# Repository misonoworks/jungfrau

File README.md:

# jungfrau
A 80-ish% Alps keyboard with an LED bar

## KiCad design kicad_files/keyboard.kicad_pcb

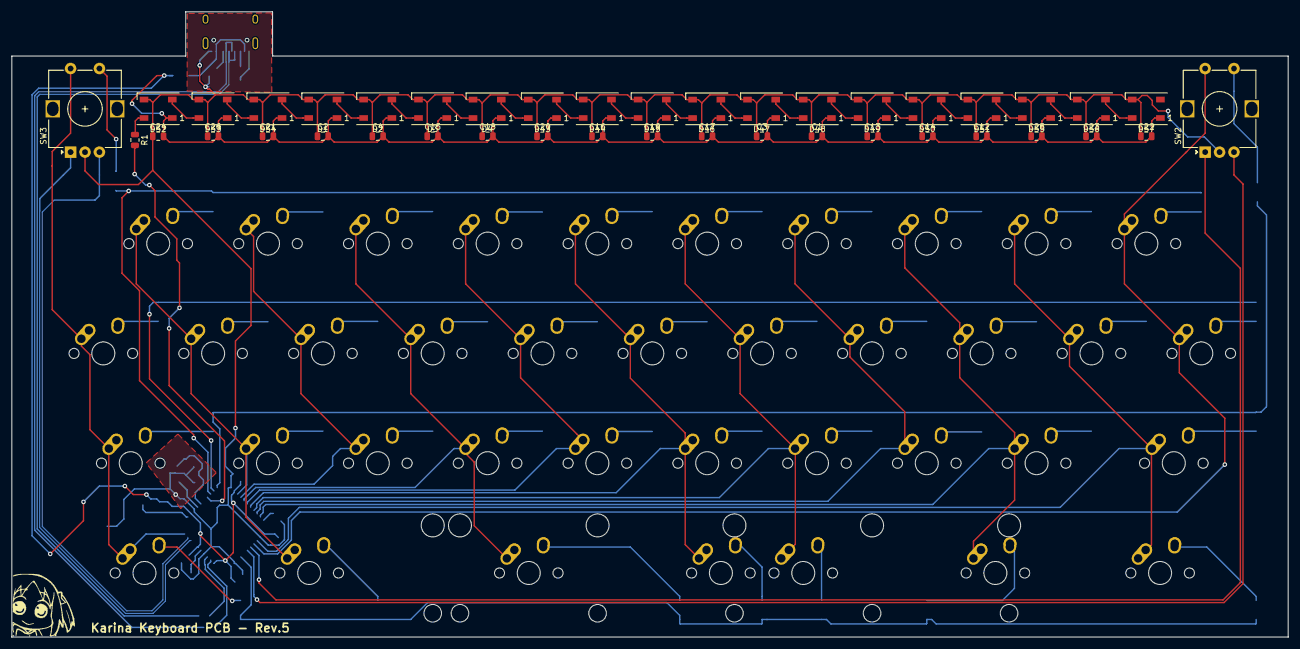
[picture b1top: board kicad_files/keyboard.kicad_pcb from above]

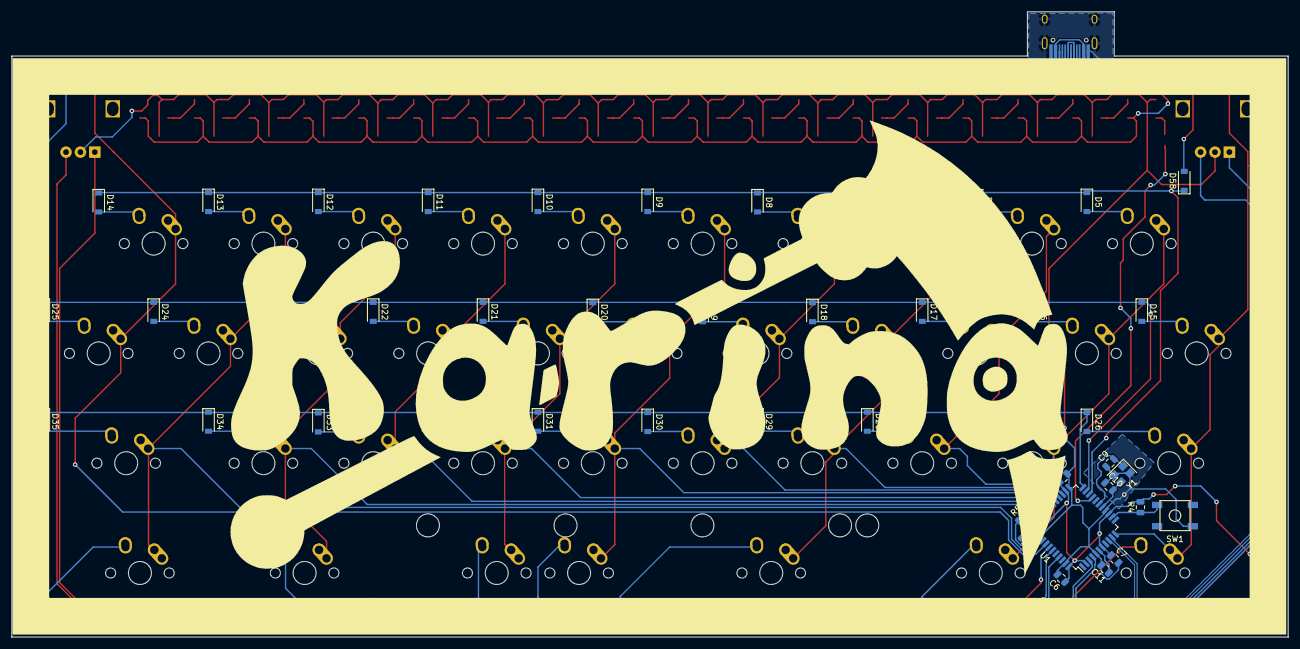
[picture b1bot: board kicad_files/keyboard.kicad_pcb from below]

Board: 2 copper layers, 221.5 x 108.5 mm, 137 parts (58 on the bottom side), 93 nets.

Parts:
C1, C2, C3, C4, C12, C13, C14, C15, C16, C17, C18, C19, C20, C21, C22, C23, C24, C25, C26: 104; C_0805_2012Metric
C5, C6, C7, C8, C11: 1uF; C_0805_2012Metric
C9, C10: 22pF; C_0805_2012Metric
D1, D2, D3, D4, D43, D44, D45, D46, D47, D48, D49, D50, D51, D52, D53, D54, D55, D56, D57: WS2812B; LED_WS2812B_PLCC4_5.0x5.0mm_P3.2mm
D5, D6, D7, D8, D9, D10, D11, D12, D13, D14, D15, D16, D17, D18, D19, D20, D21, D22, D23, D24, D25, D26, D27, D28, D29, D30, D31, D32, D33, D34, D35, D36, D37, D38, D39, D40, D41, D42, D58, D59: D_Small; D_SOD-123
F1: Polyfuse_Small; Fuse_1206_3216Metric
K_A1: MX-NoLED; MX-1U-NoLED
K_APO1: MX-NoLED; MX-1U-NoLED
K_B1: MX-NoLED; MX-1U-NoLED
K_C1: MX-NoLED; MX-1U-NoLED
K_D1: MX-NoLED; MX-1U-NoLED
K_E1: MX-NoLED; MX-1U-NoLED
K_F1: MX-NoLED; MX-1U-NoLED
K_G1: MX-NoLED; MX-1U-NoLED
K_H1: MX-NoLED; MX-1U-NoLED
K_I1: MX-NoLED; MX-1U-NoLED
K_J1: MX-NoLED; MX-1U-NoLED
K_K1: MX-NoLED; MX-1U-NoLED
K_L1: MX-NoLED; MX-1U-NoLED
K_LCTRL1: MX-NoLED; MX-1.75U-NoLED
K_M1: MX-NoLED; MX-1U-NoLED
K_META1: MX-NoLED; MX-1.75U-NoLED
K_N1: MX-NoLED; MX-1U-NoLED
K_O1: MX-NoLED; MX-1U-NoLED
K_P1: MX-NoLED; MX-1U-NoLED
K_PERIOD1: MX-NoLED; MX-1U-NoLED
K_Q1: MX-NoLED; MX-1U-NoLED
K_R1: MX-NoLED; MX-1U-NoLED
K_S1: MX-NoLED; MX-1U-NoLED
K_SHIFT1, K_SHIFT2: MX-NoLED; MX-1.5U-NoLED
K_SPACEBARSIX1: MX-NoLED; MX-6.25U-ReversedStabilizers-NoLED
K_SPBALT1: MX-NoLED; MX-1.25U-NoLED
K_SPBDEL1: MX-NoLED; MX-2.25U-ReversedStabilizers-NoLED
K_SPBSPACE1: MX-NoLED; MX-2.75U-ReversedStabilizers-NoLED
K_SUPER1: MX-NoLED; MX-1.25U-NoLED
K_T1: MX-NoLED; MX-1U-NoLED
K_TAB1: MX-NoLED; MX-1U-NoLED
K_U1: MX-NoLED; MX-1U-NoLED
K_V1: MX-NoLED; MX-1U-NoLED
K_W1: MX-NoLED; MX-1U-NoLED
K_X1: MX-NoLED; MX-1U-NoLED
K_Y1: MX-NoLED; MX-1U-NoLED
K_Z1: MX-NoLED; MX-1U-NoLED
R1: 500ohm; R_0805_2012Metric
R2, R3: 22; R_0805_2012Metric
R4, R5: 10K; R_0805_2012Metric
R6, R7: 5.1k; R_0805_2012Metric
SW1: SW_Push; SKQG-1155865
SW2, SW3: Rotary_Encoder_Switch; RotaryEncoder_Alps_EC12E-Switch_Vertical_H20mm
U1: ATmega32U4-AU; TQFP-44_10x10mm_P0.8mm
USB1: HRO-TYPE-C-31-M-12; HRO-TYPE-C-31-M-12-HandSoldering
Y1: Crystal_GND24_Small; Crystal_SMD_3225-4Pin_3.2x2.5mm

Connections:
2812b_data: R1.2, U1.19
+5V: C1.2, C2.2, C3.2, C4.2, C5.1, C6.1, C7.1, C8.1, C12.2, C13.2, C14.2, C15.2, C16.2, C17.2, C18.2, C19.2, C20.2, C21.2, C22.2, C23.2, C24.2, C25.2, C26.2, D1.1, D2.1, D3.1, D4.1, D43.1, D44.1, D45.1, D46.1, D47.1, D48.1, D49.1, D50.1, D51.1, D52.1, D53.1, D54.1, D55.1, D56.1, D57.1, F1.1, R4.2, U1.2, U1.7, U1.14, U1.24, U1.34, U1.44
D+: R3.2, USB1.6, USB1.8
D-: R2.2, USB1.5, USB1.7
Encoder1D+: SW3.A, U1.9
Encoder1D-: SW3.B, U1.10
Encoder2D+: SW2.A, U1.38
Encoder2D-: SW2.B, U1.39
GND: C1.1, C2.1, C3.1, C4.1, C5.2, C6.2, C7.2, C8.2, C9.1, C10.1, C11.2, C12.1, C13.1, C14.1, C15.1, C16.1, C17.1, C18.1, C19.1, C20.1, C21.1, C22.1, C23.1, C24.1, C25.1, C26.1, D1.3, D2.3, D3.3, D4.3, D43.3, D44.3, D45.3, D46.3, D47.3, D48.3, D49.3, D50.3, D51.3, D52.3, D53.3, D54.3, D55.3, D56.3, D57.3, R5.1, R6.1, R7.1, SW1.1, SW2.C, SW3.C, U1.5, U1.15, U1.23, U1.35, U1.43, USB1.1, USB1.12, USB1.13, Y1.2, Y1.4
unnamed: C9.2, U1.17, Y1.1
unnamed: C10.2, U1.16, Y1.3
unnamed: C11.1, U1.6
unnamed: D1.2, D2.4
unnamed: D1.4, D54.2
unnamed: D2.2, D3.4
unnamed: D3.2, D4.4
unnamed: D4.2, D43.4
unnamed: D5.2, K_Q1.2
unnamed: D6.2, K_W1.2
unnamed: D7.2, K_E1.2
unnamed: D8.2, K_R1.2
unnamed: D9.2, K_T1.2
unnamed: D10.2, K_Y1.2
unnamed: D11.2, K_U1.2
unnamed: D12.2, K_I1.2
unnamed: D13.2, K_O1.2
unnamed: D14.2, K_P1.2
unnamed: D15.2, K_TAB1.2
unnamed: D16.2, K_A1.2
unnamed: D17.2, K_S1.2
unnamed: D18.2, K_D1.2
unnamed: D19.2, K_F1.2
unnamed: D20.2, K_G1.2
unnamed: D21.2, K_H1.2
unnamed: D22.2, K_J1.2
unnamed: D23.2, K_K1.2
unnamed: D24.2, K_L1.2
unnamed: D25.2, K_APO1.2
unnamed: D26.2, K_SHIFT1.2
unnamed: D27.2, K_Z1.2
unnamed: D28.2, K_X1.2
unnamed: D29.2, K_C1.2
unnamed: D30.2, K_V1.2
unnamed: D31.2, K_B1.2
unnamed: D32.2, K_N1.2
unnamed: D33.2, K_M1.2
unnamed: D34.2, K_PERIOD1.2
unnamed: D35.2, K_SHIFT2.2
unnamed: D36.2, K_LCTRL1.2
unnamed: D37.2, K_SUPER1.2
unnamed: D38.2, K_SPBSPACE1.2
unnamed: D39.2, K_SPACEBARSIX1.2
unnamed: D40.2, K_SPBDEL1.2
unnamed: D41.2, K_SPBALT1.2
unnamed: D42.2, K_META1.2
unnamed: D43.2, D44.4
unnamed: D44.2, D45.4
unnamed: D45.2, D46.4
unnamed: D46.2, D47.4
unnamed: D47.2, D48.4
unnamed: D48.2, D49.4
unnamed: D49.2, D50.4
unnamed: D50.2, D51.4
unnamed: D51.2, D55.4
unnamed: D52.2, D53.4
unnamed: D52.4, R1.1
unnamed: D53.2, D54.4
unnamed: D55.2, D56.4
unnamed: D56.2, D57.4
unnamed: D58.2, SW3.S2
unnamed: D59.2, SW2.S2
unnamed: R2.1, U1.3
unnamed: R3.1, U1.4
unnamed: R4.1, SW1.2, U1.13
unnamed: R5.2, U1.33
unnamed: R6.2, USB1.4
unnamed: R7.2, USB1.10
VCC: F1.2, USB1.2, USB1.11
col0: K_LCTRL1.1, K_SHIFT1.1, K_TAB1.1, SW3.S1, U1.11
col1: K_A1.1, K_Q1.1, K_SUPER1.1, K_Z1.1, U1.25
col2: K_S1.1, K_W1.1, K_X1.1, U1.26
col3: K_C1.1, K_D1.1, K_E1.1, K_SPBSPACE1.1, U1.27
col4: K_F1.1, K_R1.1, K_V1.1, U1.28
col5: K_B1.1, K_G1.1, K_SPACEBARSIX1.1, K_T1.1, U1.29
col6: K_H1.1, K_N1.1, K_SPBDEL1.1, K_Y1.1, U1.30
col7: K_J1.1, K_M1.1, K_U1.1, U1.31
col8: K_I1.1, K_K1.1, K_PERIOD1.1, K_SPBALT1.1, U1.32
col9: K_L1.1, K_META1.1, K_O1.1, K_SHIFT2.1, U1.36
col10: K_APO1.1, K_P1.1, SW2.S1, U1.37
row0: D5.1, D6.1, D7.1, D8.1, D9.1, D10.1, D11.1, D12.1, D13.1, D14.1, D58.1, U1.20
row1: D15.1, D16.1, D17.1, D18.1, D19.1, D20.1, D21.1, D22.1, D23.1, D24.1, D25.1, U1.21
row2: D26.1, D27.1, D28.1, D29.1, D30.1, D31.1, D32.1, D33.1, D34.1, D35.1, D59.1, U1.22
row3: D36.1, D37.1, D38.1, D39.1, D40.1, D41.1, D42.1, U1.41

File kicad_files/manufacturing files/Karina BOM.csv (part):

Date:,09/23/20 0:31:32,,,,,,
Tool:,Eeschema (5.1.5)-3,,,,,,
Component Count:,137,,,,,,
Ref,Value,Footprint,Datasheet,Manufacturer,Vendor,LCSC Part No.,Manufacturer Part No.
C1,104,Capacitor_SMD:C_0805_2012Metric,~,YAGEO,LCSC,C49678,CC0805KRX7R9BB104
C2,104,Capacitor_SMD:C_0805_2012Metric,~,YAGEO,LCSC,C49678,CC0805KRX7R9BB104
C3,104,Capacitor_SMD:C_0805_2012Metric,~,YAGEO,LCSC,C49678,CC0805KRX7R9BB104
C4,104,Capacitor_SMD:C_0805_2012Metric,~,YAGEO,LCSC,C49678,CC0805KRX7R9BB104
C5,1uF,Capacitor_SMD:C_0805_2012Metric,~,Samsung Electro-Mechanics,LCSC,C28323,CL21B105KBFNNNE
C6,1uF,Capacitor_SMD:C_0805_2012Metric,~,Samsung Electro-Mechanics,LCSC,C28323,CL21B105KBFNNNE
C7,1uF,Capacitor_SMD:C_0805_2012Metric,~,Samsung Electro-Mechanics,LCSC,C28323,CL21B105KBFNNNE
C8,1uF,Capacitor_SMD:C_0805_2012Metric,~,Samsung Electro-Mechanics,LCSC,C28323,CL21B105KBFNNNE
C9,22pF,Capacitor_SMD:C_0805_2012Metric,~,Samsung Electro-Mechanics,LCSC,C1804,CL21C220JBANNNC
C10,22pF,Capacitor_SMD:C_0805_2012Metric,~,Samsung Electro-Mechanics,LCSC,C1804,CL21C220JBANNNC
C11,1uF,Capacitor_SMD:C_0805_2012Metric,~,Samsung Electro-Mechanics,LCSC,C28323,CL21B105KBFNNNE
C12,104,Capacitor_SMD:C_0805_2012Metric,~,YAGEO,LCSC,C49678,CC0805KRX7R9BB104
C13,104,Capacitor_SMD:C_0805_2012Metric,~,YAGEO,LCSC,C49678,CC0805KRX7R9BB104
C14,104,Capacitor_SMD:C_0805_2012Metric,~,YAGEO,LCSC,C49678,CC0805KRX7R9BB104
C15,104,Capacitor_SMD:C_0805_2012Metric,~,YAGEO,LCSC,C49678,CC0805KRX7R9BB104
C16,104,Capacitor_SMD:C_0805_2012Metric,~,YAGEO,LCSC,C49678,CC0805KRX7R9BB104
C17,104,Capacitor_SMD:C_0805_2012Metric,~,YAGEO,LCSC,C49678,CC0805KRX7R9BB104
C18,104,Capacitor_SMD:C_0805_2012Metric,~,YAGEO,LCSC,C49678,CC0805KRX7R9BB104
C19,104,Capacitor_SMD:C_0805_2012Metric,~,YAGEO,LCSC,C49678,CC0805KRX7R9BB104
C20,104,Capacitor_SMD:C_0805_2012Metric,~,YAGEO,LCSC,C49678,CC0805KRX7R9BB104
C21,104,Capacitor_SMD:C_0805_2012Metric,~,YAGEO,LCSC,C49678,CC0805KRX7R9BB104
C22,104,Capacitor_SMD:C_0805_2012Metric,~,YAGEO,LCSC,C49678,CC0805KRX7R9BB104
C23,104,Capacitor_SMD:C_0805_2012Metric,~,YAGEO,LCSC,C49678,CC0805KRX7R9BB104
C24,104,Capacitor_SMD:C_0805_2012Metric,~,YAGEO,LCSC,C49678,CC0805KRX7R9BB104
C25,104,Capacitor_SMD:C_0805_2012Metric,~,YAGEO,LCSC,C49678,CC0805KRX7R9BB104
C26,104,Capacitor_SMD:C_0805_2012Metric,~,YAGEO,LCSC,C49678,CC0805KRX7R9BB104
D5,D_Small,Diode_SMD:D_SOD-123,~,Shadong Jingdao Microelectronics,LCSC,C108803,1N4007W
D6,D_Small,Diode_SMD:D_SOD-123,~,Shadong Jingdao Microelectronics,LCSC,C108803,1N4007W
D7,D_Small,Diode_SMD:D_SOD-123,~,Shadong Jingdao Microelectronics,LCSC,C108803,1N4007W
D8,D_Small,Diode_SMD:D_SOD-123,~,Shadong Jingdao Microelectronics,LCSC,C108803,1N4007W
D9,D_Small,Diode_SMD:D_SOD-123,~,Shadong Jingdao Microelectronics,LCSC,C108803,1N4007W
D10,D_Small,Diode_SMD:D_SOD-123,~,Shadong Jingdao Microelectronics,LCSC,C108803,1N4007W
D11,D_Small,Diode_SMD:D_SOD-123,~,Shadong Jingdao Microelectronics,LCSC,C108803,1N4007W
D12,D_Small,Diode_SMD:D_SOD-123,~,Shadong Jingdao Microelectronics,LCSC,C108803,1N4007W
D13,D_Small,Diode_SMD:D_SOD-123,~,Shadong Jingdao Microelectronics,LCSC,C108803,1N4007W
D14,D_Small,Diode_SMD:D_SOD-123,~,Shadong Jingdao Microelectronics,LCSC,C108803,1N4007W
D15,D_Small,Diode_SMD:D_SOD-123,~,Shadong Jingdao Microelectronics,LCSC,C108803,1N4007W
D16,D_Small,Diode_SMD:D_SOD-123,~,Shadong Jingdao Microelectronics,LCSC,C108803,1N4007W
D17,D_Small,Diode_SMD:D_SOD-123,~,Shadong Jingdao Microelectronics,LCSC,C108803,1N4007W
D18,D_Small,Diode_SMD:D_SOD-123,~,Shadong Jingdao Microelectronics,LCSC,C108803,1N4007W
D19,D_Small,Diode_SMD:D_SOD-123,~,Shadong Jingdao Microelectronics,LCSC,C108803,1N4007W
D20,D_Small,Diode_SMD:D_SOD-123,~,Shadong Jingdao Microelectronics,LCSC,C108803,1N4007W
D21,D_Small,Diode_SMD:D_SOD-123,~,Shadong Jingdao Microelectronics,LCSC,C108803,1N4007W
D22,D_Small,Diode_SMD:D_SOD-123,~,Shadong Jingdao Microelectronics,LCSC,C108803,1N4007W
D23,D_Small,Diode_SMD:D_SOD-123,~,Shadong Jingdao Microelectronics,LCSC,C108803,1N4007W
D24,D_Small,Diode_SMD:D_SOD-123,~,Shadong Jingdao Microelectronics,LCSC,C108803,1N4007W
D25,D_Small,Diode_SMD:D_SOD-123,~,Shadong Jingdao Microelectronics,LCSC,C108803,1N4007W
D26,D_Small,Diode_SMD:D_SOD-123,~,Shadong Jingdao Microelectronics,LCSC,C108803,1N4007W
D27,D_Small,Diode_SMD:D_SOD-123,~,Shadong Jingdao Microelectronics,LCSC,C108803,1N4007W
D28,D_Small,Diode_SMD:D_SOD-123,~,Shadong Jingdao Microelectronics,LCSC,C108803,1N4007W
D29,D_Small,Diode_SMD:D_SOD-123,~,Shadong Jingdao Microelectronics,LCSC,C108803,1N4007W
D30,D_Small,Diode_SMD:D_SOD-123,~,Shadong Jingdao Microelectronics,LCSC,C108803,1N4007W
D31,D_Small,Diode_SMD:D_SOD-123,~,Shadong Jingdao Microelectronics,LCSC,C108803,1N4007W
D32,D_Small,Diode_SMD:D_SOD-123,~,Shadong Jingdao Microelectronics,LCSC,C108803,1N4007W
D33,D_Small,Diode_SMD:D_SOD-123,~,Shadong Jingdao Microelectronics,LCSC,C108803,1N4007W
D34,D_Small,Diode_SMD:D_SOD-123,~,Shadong Jingdao Microelectronics,LCSC,C108803,1N4007W
D35,D_Small,Diode_SMD:D_SOD-123,~,Shadong Jingdao Microelectronics,LCSC,C108803,1N4007W
D36,D_Small,Diode_SMD:D_SOD-123,~,Shadong Jingdao Microelectronics,LCSC,C108803,1N4007W
D37,D_Small,Diode_SMD:D_SOD-123,~,Shadong Jingdao Microelectronics,LCSC,C108803,1N4007W
D38,D_Small,Diode_SMD:D_SOD-123,~,Shadong Jingdao Microelectronics,LCSC,C108803,1N4007W
D39,D_Small,Diode_SMD:D_SOD-123,~,Shadong Jingdao Microelectronics,LCSC,C108803,1N4007W
D40,D_Small,Diode_SMD:D_SOD-123,~,Shadong Jingdao Microelectronics,LCSC,C108803,1N4007W
D41,D_Small,Diode_SMD:D_SOD-123,~,Shadong Jingdao Microelectronics,LCSC,C108803,1N4007W
D42,D_Small,Diode_SMD:D_SOD-123,~,Shadong Jingdao Microelectronics,LCSC,C108803,1N4007W
D58,D_Small,Diode_SMD:D_SOD-123,~,Shadong Jingdao Microelectronics,LCSC,C108803,1N4007W
D59,D_Small,Diode_SMD:D_SOD-123,~,Shadong Jingdao Microelectronics,LCSC,C108803,1N4007W
F1,Polyfuse_Small,Fuse:Fuse_1206_3216Metric,~,Littelfuse,LCSC,C151162,1206L050/15YR
LED1,WS2812B,LED_SMD:LED_WS2812B_PLCC4_5.0x5.0mm_P3.2mm,https://cdn-shop.adafruit.com/datasheets/WS2812B.pdf,Worldsemi,LCSC,C114586,WS2812B-B
LED2,WS2812B,LED_SMD:LED_WS2812B_PLCC4_5.0x5.0mm_P3.2mm,https://cdn-shop.adafruit.com/datasheets/WS2812B.pdf,Worldsemi,LCSC,C114586,WS2812B-B
LED3,WS2812B,LED_SMD:LED_WS2812B_PLCC4_5.0x5.0mm_P3.2mm,https://cdn-shop.adafruit.com/datasheets/WS2812B.pdf,Worldsemi,LCSC,C114586,WS2812B-B
LED4,WS2812B,LED_SMD:LED_WS2812B_PLCC4_5.0x5.0mm_P3.2mm,https://cdn-shop.adafruit.com/datasheets/WS2812B.pdf,Worldsemi,LCSC,C114586,WS2812B-B
LED5,WS2812B,LED_SMD:LED_WS2812B_PLCC4_5.0x5.0mm_P3.2mm,https://cdn-shop.adafruit.com/datasheets/WS2812B.pdf,Worldsemi,LCSC,C114586,WS2812B-B
LED6,WS2812B,LED_SMD:LED_WS2812B_PLCC4_5.0x5.0mm_P3.2mm,https://cdn-shop.adafruit.com/datasheets/WS2812B.pdf,Worldsemi,LCSC,C114586,WS2812B-B
LED7,WS2812B,LED_SMD:LED_WS2812B_PLCC4_5.0x5.0mm_P3.2mm,https://cdn-shop.adafruit.com/datasheets/WS2812B.pdf,Worldsemi,LCSC,C114586,WS2812B-B
LED8,WS2812B,LED_SMD:LED_WS2812B_PLCC4_5.0x5.0mm_P3.2mm,https://cdn-shop.adafruit.com/datasheets/WS2812B.pdf,Worldsemi,LCSC,C114586,WS2812B-B
LED9,WS2812B,LED_SMD:LED_WS2812B_PLCC4_5.0x5.0mm_P3.2mm,https://cdn-shop.adafruit.com/datasheets/WS2812B.pdf,Worldsemi,LCSC,C114586,WS2812B-B
LED10,WS2812B,LED_SMD:LED_WS2812B_PLCC4_5.0x5.0mm_P3.2mm,https://cdn-shop.adafruit.com/datasheets/WS2812B.pdf,Worldsemi,LCSC,C114586,WS2812B-B
LED11,WS2812B,LED_SMD:LED_WS2812B_PLCC4_5.0x5.0mm_P3.2mm,https://cdn-shop.adafruit.com/datasheets/WS2812B.pdf,Worldsemi,LCSC,C114586,WS2812B-B
LED12,WS2812B,LED_SMD:LED_WS2812B_PLCC4_5.0x5.0mm_P3.2mm,https://cdn-shop.adafruit.com/datasheets/WS2812B.pdf,Worldsemi,LCSC,C114586,WS2812B-B
LED13,WS2812B,LED_SMD:LED_WS2812B_PLCC4_5.0x5.0mm_P3.2mm,https://cdn-shop.adafruit.com/datasheets/WS2812B.pdf,Worldsemi,LCSC,C114586,WS2812B-B
LED14,WS2812B,LED_SMD:LED_WS2812B_PLCC4_5.0x5.0mm_P3.2mm,https://cdn-shop.adafruit.com/datasheets/WS2812B.pdf,Worldsemi,LCSC,C114586,WS2812B-B
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
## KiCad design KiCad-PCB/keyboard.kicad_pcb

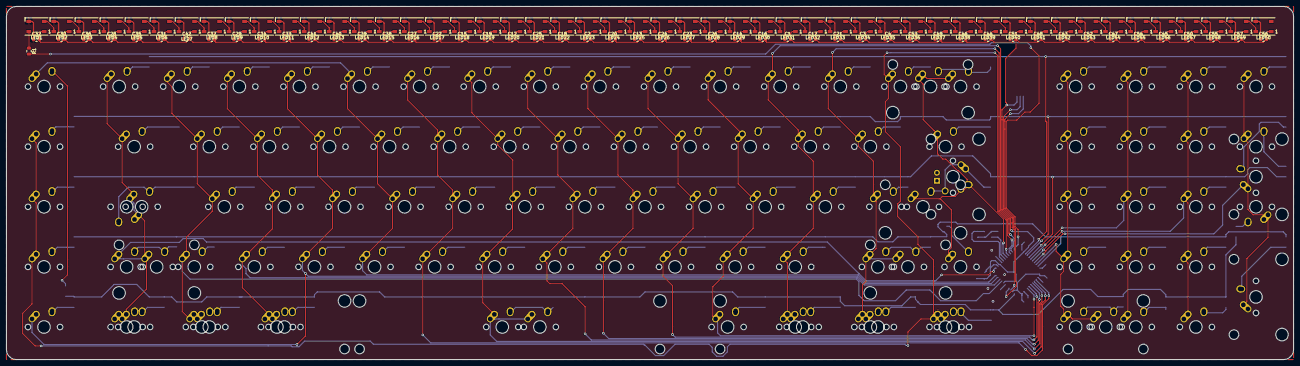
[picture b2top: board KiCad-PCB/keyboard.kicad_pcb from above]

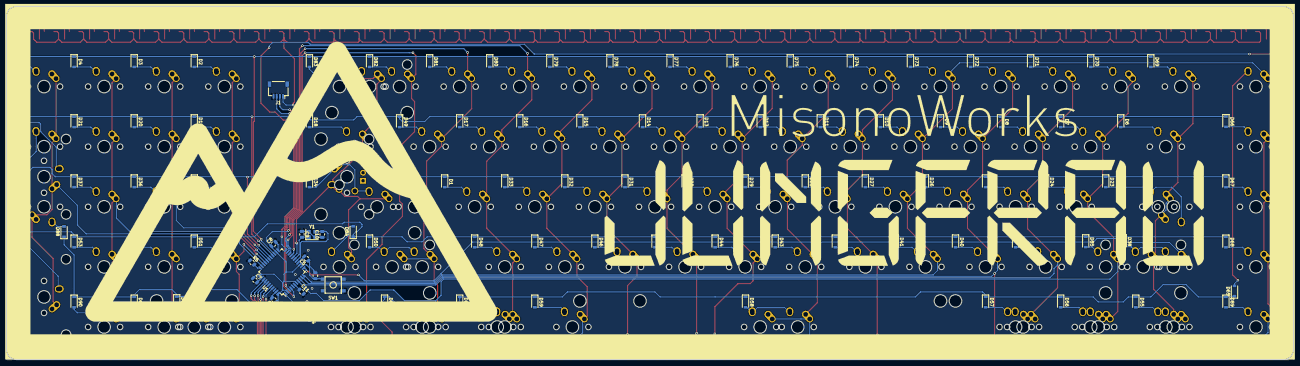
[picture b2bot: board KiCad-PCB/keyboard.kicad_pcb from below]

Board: 2 copper layers, 408.0 x 111.9 mm, 307 parts (103 on the bottom side), 174 nets.

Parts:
C1, C2, C3, C4, C12, C13, C14, C15, C16, C17, C18, C19, C20, C21, C22, C23, C24, C25, C26, C27, C28, C29, C30, C31, C32, C33, C34, C35, C36, C37, C38, C39, C40, C41, C42, C43, C44, C45, C46, C47, C48, C49, C50, C51, C52, C53, C54, C55, C56, C57: 104; C_0805_2012Metric
C5, C6, C7, C8, C11: 1uF; C_0805_2012Metric
C9, C10: 22pF; C_0805_2012Metric
D1, D2, D3, D4, D5, D6, D7, D8, D9, D10, D11, D12, D13, D14, D15, D16, D17, D18, D19, D20, D21, D22, D23, D24, D25, D26, D27, D28, D29, D30, D31, D32, D33, D34, D35, D36, D37, D38, D39, D40, D41, D42, D43, D44, D45, D46, D47, D48, D49, D50, D51, D52, D53, D54, D55, D56, D57, D58, D59, D60, D61, D62, D63, D64, D65, D66, D67, D68, D69, D70, D71, D72, D73, D74, D75, D76, D77, D78, D79, D80, D81, D82, D83, D84, D85, D86, D87, D88, D89, D90: SOD-123; D_SOD-123
J1: Conn_01x04_Female; JST_SH_SM04B-SRSS-TB_1x04-1MP_P1.00mm_Horizontal
LED1, LED2, LED3, LED4, LED5, LED6, LED7, LED8, LED9, LED10, LED11, LED12, LED13, LED14, LED15, LED16, LED17, LED18, LED19, LED20, LED21, LED22, LED23, LED24, LED25, LED26, LED27, LED28, LED29, LED30, LED31, LED32, LED33, LED34, LED35, LED36, LED37, LED38, LED39, LED40, LED41, LED42, LED43, LED44, LED45, LED46, LED47, LED48, LED49, LED50: WS2812B; LED_WS2812B_PLCC4_5.0x5.0mm_P3.2mm
MACRO1, MACRO2, MACRO3, MACRO4, MACRO5: MX-NoLED; MX-1U-NoLED
MX1, MX55, MX56, MX57, MX59, MX60, MX61, MX65, MX96: MX-NoLED; MX-1.25U-NoLED
MX2, MX3, MX4, MX5, MX7, MX8, MX9, MX10, MX11, MX12, MX13, MX14, MX15, MX16, MX17, MX19, MX20, MX21, MX24, MX25, MX26, MX27, MX28, MX29, MX30, MX31, MX32, MX33, MX35, MX36, MX37, MX39, MX40, MX41, MX42, MX43, MX44, MX45, MX46, MX47, MX48, MX49, MX51, MX52, MX53, MX63, MX64, MX70, MX71, MX72, MX73, MX74, MX75, MX76, MX77, MX78, MX79, MX80, MX81, MX82, MX83, MX84, MX88, MX91, MX95, MX97, MX98, MX99, MX100, MX101, MX102: MX-NoLED; MX-1U-NoLED
MX6, MX18, MX87, MX89, MX90, MX92: MX-NoLED; MX-1.5U-NoLED
MX22, MX54, MX85: MX-NoLED; MX-2U-NoLED
MX23, MX94: MX-NoLED; MX-1.75U-NoLED
MX34, MX38: MX-NoLED; MX-2.25U-NoLED
MX50: MX-NoLED; MX-2.75U-NoLED
MX58: MX-NoLED; MX-6.25U-ReversedStabilizers-NoLED
MX62: MX-NoLED; MX-2U-ReversedStabilizers-NoLED
MX86: MX-NoLED; MX-7U-ReversedStabilizers-NoLED
MX93: MX-NoLED; MX-ISO
R1: 500ohm; R_0805_2012Metric
R4, R5: 10K; R_0805_2012Metric
SW1: SW_Push; SKQG-1155865
U1: ATmega32U4-AU; TQFP-44_10x10mm_P0.8mm
Y1: Crystal_GND24_Small; Crystal_SMD_3225-4Pin_3.2x2.5mm

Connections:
2812b_data: R1.2, U1.22
2821O: LED35.2, LED36.4
+5V: C1.2, C2.2, C3.2, C4.2, C5.1, C6.1, C7.1, C8.1, C12.2, C13.2, C14.2, C15.2, C16.2, C17.2, C18.2, C19.2, C20.2, C21.2, C22.2, C23.2, C24.2, C25.2, C26.2, C27.2, C28.2, C29.2, C30.2, C31.2, C32.2, C33.2, C34.2, C35.2, C36.2, C37.2, C38.2, C39.2, C40.2, C41.2, C42.2, C43.2, C44.2, C45.2, C46.2, C47.2, C48.2, C49.2, C50.2, C51.2, C52.2, C53.2, C54.2, C55.2, C56.2, C57.2, J1.1, LED1.1, LED2.1, LED3.1, LED4.1, LED5.1, LED6.1, LED7.1, LED8.1, LED9.1, LED10.1, LED11.1, LED12.1, LED13.1, LED14.1, LED15.1, LED16.1, LED17.1, LED18.1, LED19.1, LED20.1, LED21.1, LED22.1, LED23.1, LED24.1, LED25.1, LED26.1, LED27.1, LED28.1, LED29.1, LED30.1, LED31.1, LED32.1, LED33.1, LED34.1, LED35.1, LED36.1, LED37.1, LED38.1, LED39.1, LED40.1, LED41.1, LED42.1, LED43.1, LED44.1, LED45.1, LED46.1, LED47.1, LED48.1, LED49.1, LED50.1, R4.2, U1.2, U1.7, U1.14, U1.24, U1.34, U1.44
D+: J1.3, U1.4
D-: J1.2, U1.3
GND: C1.1, C2.1, C3.1, C4.1, C5.2, C6.2, C7.2, C8.2, C9.1, C10.1, C11.2, C12.1, C13.1, C14.1, C15.1, C16.1, C17.1, C18.1, C19.1, C20.1, C21.1, C22.1, C23.1, C24.1, C25.1, C26.1, C27.1, C28.1, C29.1, C30.1, C31.1, C32.1, C33.1, C34.1, C35.1, C36.1, C37.1, C38.1, C39.1, C40.1, C41.1, C42.1, C43.1, C44.1, C45.1, C46.1, C47.1, C48.1, C49.1, C50.1, C51.1, C52.1, C53.1, C54.1, C55.1, C56.1, C57.1, J1.4, LED1.3, LED2.3, LED3.3, LED4.3, LED5.3, LED6.3, LED7.3, LED8.3, LED9.3, LED10.3, LED11.3, LED12.3, LED13.3, LED14.3, LED15.3, LED16.3, LED17.3, LED18.3, LED19.3, LED20.3, LED21.3, LED22.3, LED23.3, LED24.3, LED25.3, LED26.3, LED27.3, LED28.3, LED29.3, LED30.3, LED31.3, LED32.3, LED33.3, LED34.3, LED35.3, LED36.3, LED37.3, LED38.3, LED39.3, LED40.3, LED41.3, LED42.3, LED43.3, LED44.3, LED45.3, LED46.3, LED47.3, LED48.3, LED49.3, LED50.3, R5.1, SW1.1, U1.5, U1.15, U1.23, U1.35, U1.43, Y1.2, Y1.4
unnamed: C9.2, U1.17, Y1.1
unnamed: C10.2, U1.16, Y1.3
unnamed: C11.1, U1.6
unnamed: D1.2, MX48.2
unnamed: D2.2, MX2.2
unnamed: D3.2, MX3.2
unnamed: D4.2, MX4.2
unnamed: D5.2, MX5.2
unnamed: D6.2, MX6.2
unnamed: D7.2, MX7.2
unnamed: D8.2, MX8.2
unnamed: D9.2, MX9.2
unnamed: D10.2, MX10.2
unnamed: D11.2, MX11.2
unnamed: D12.2, MX12.2
unnamed: D13.2, MX13.2
unnamed: D14.2, MX14.2
unnamed: D15.2, MX15.2
unnamed: D16.2, MX16.2
unnamed: D17.2, MX17.2
unnamed: D18.2, MX18.2
unnamed: D19.2, MX19.2
unnamed: D20.2, MX20.2
unnamed: D21.2, MX21.2
unnamed: D22.2, MX22.2
unnamed: D23.2, MX1.2, MX23.2
unnamed: D24.2, MX24.2
unnamed: D25.2, MX25.2
unnamed: D26.2, MX26.2
unnamed: D27.2, MX27.2
unnamed: D28.2, MX28.2
unnamed: D29.2, MX29.2
unnamed: D30.2, MX30.2
unnamed: D31.2, MX31.2
unnamed: D32.2, MX32.2
unnamed: D33.2, MX33.2
unnamed: D34.2, MX34.2, MX93.2
unnamed: D35.2, MX35.2
unnamed: D36.2, MX36.2
unnamed: D37.2, MX37.2
unnamed: D38.2, MX38.2, MX96.2
unnamed: D39.2, MX39.2
unnamed: D40.2, MX40.2
unnamed: D41.2, MX41.2
unnamed: D42.2, MX42.2
unnamed: D43.2, MX43.2
unnamed: D44.2, MX44.2
unnamed: D45.2, MX45.2
unnamed: D46.2, MX46.2
unnamed: D47.2, MX47.2
unnamed: D48.2, MX49.2
unnamed: D49.2, MX64.2
unnamed: D50.2, MX50.2, MX94.2
unnamed: D51.2, MX51.2
unnamed: D52.2, MX52.2
unnamed: D53.2, MX53.2
unnamed: D54.2, MX54.2
unnamed: D55.2, MX55.2, MX87.2
unnamed: D56.2, MX56.2, MX88.2
unnamed: D57.2, MX57.2, MX89.2
unnamed: D58.2, MX58.2, MX86.2
unnamed: D59.2, MX59.2
unnamed: D60.2, MX60.2, MX90.2
unnamed: D61.2, MX61.2, MX91.2
unnamed: D62.2, MX62.2, MX101.2
unnamed: D63.2, MX63.2
unnamed: D64.2, MX65.2, MX92.2
unnamed: D65.2, MACRO1.2
unnamed: D66.2, MACRO2.2
unnamed: D67.2, MACRO3.2
unnamed: D68.2, MACRO4.2
unnamed: D69.2, MX70.2
unnamed: D70.2, MX71.2
unnamed: D71.2, MX72.2
unnamed: D72.2, MX73.2
unnamed: D73.2, MX74.2
unnamed: D74.2, MX75.2
unnamed: D75.2, MX76.2
unnamed: D76.2, MX77.2
unnamed: D77.2, MX78.2
unnamed: D78.2, MX79.2
unnamed: D79.2, MX80.2
unnamed: D80.2, MX81.2
unnamed: D81.2, MX82.2
unnamed: D82.2, MX83.2
unnamed: D83.2, MX84.2, MX85.2
unnamed: D84.2, MX95.2
unnamed: D85.2, MX97.2
unnamed: D86.2, MX98.2
unnamed: D87.2, MX99.2
unnamed: D88.2, MX100.2
unnamed: D89.2, MACRO5.2
unnamed: D90.2, MX102.2
unnamed: LED1.2, LED2.4
unnamed: LED1.4, R1.1
unnamed: LED2.2, LED3.4
unnamed: LED3.2, LED4.4
unnamed: LED4.2, LED5.4
unnamed: LED5.2, LED6.4
unnamed: LED6.2, LED7.4
unnamed: LED7.2, LED8.4
unnamed: LED8.2, LED9.4
unnamed: LED10.2, LED11.4
unnamed: LED9.2, LED10.4
unnamed: LED11.2, LED12.4
unnamed: LED12.2, LED13.4
unnamed: LED13.2, LED14.4
unnamed: LED14.2, LED15.4
unnamed: LED15.2, LED16.4
unnamed: LED16.2, LED17.4
unnamed: LED17.2, LED18.4
unnamed: LED18.2, LED19.4
unnamed: LED19.2, LED20.4
unnamed: LED20.2, LED21.4
unnamed: LED21.2, LED22.4
unnamed: LED22.2, LED23.4
unnamed: LED23.2, LED24.4
unnamed: LED24.2, LED25.4
unnamed: LED25.2, LED26.4
unnamed: LED26.2, LED27.4
unnamed: LED27.2, LED28.4
unnamed: LED28.2, LED29.4
unnamed: LED29.2, LED30.4
unnamed: LED30.2, LED31.4
unnamed: LED31.2, LED32.4
unnamed: LED32.2, LED33.4
unnamed: LED33.2, LED34.4
unnamed: LED34.2, LED35.4
unnamed: LED36.2, LED37.4
unnamed: LED37.2, LED38.4
unnamed: LED38.2, LED39.4
unnamed: LED39.2, LED40.4
unnamed: LED40.2, LED41.4
unnamed: LED41.2, LED42.4
unnamed: LED42.2, LED43.4
unnamed: LED43.2, LED44.4
unnamed: LED44.2, LED45.4
unnamed: LED45.2, LED46.4
unnamed: LED46.2, LED47.4
unnamed: LED47.2, LED48.4
unnamed: LED48.2, LED49.4
unnamed: LED49.2, LED50.4
unnamed: R4.1, SW1.2, U1.13
unnamed: R5.2, U1.33
col0: MX1.1, MX6.1, MX23.1, MX38.1, MX55.1, MX70.1, MX87.1, MX96.1, U1.12
col1: MX7.1, MX24.1, MX56.1, MX71.1, MX88.1, MX97.1, U1.8
col2: MX8.1, MX25.1, MX39.1, MX57.1, MX72.1, MX89.1, U1.9
col3: MACRO5.1, MX9.1, MX26.1, MX40.1, MX73.1, U1.10
col4: MACRO1.1, MX10.1, MX27.1, MX41.1, MX74.1, U1.11
col5: MX11.1, MX28.1, MX42.1, MX75.1, U1.36
col6: MX12.1, MX29.1, MX43.1, MX58.1, MX76.1, MX86.1, U1.37
col7: MX13.1, MX30.1, MX44.1, MX77.1, U1.38
col8: MX14.1, MX31.1, MX45.1, MX78.1, U1.39
col9: MX15.1, MX32.1, MX46.1, MX79.1, U1.40
col10: MX16.1, MX33.1, MX47.1, MX59.1, MX80.1, U1.41
col11: MX17.1, MX48.1, MX49.1, MX60.1, MX81.1, MX90.1, U1.21
col12: MX50.1, MX61.1, MX64.1, MX82.1, MX91.1, MX94.1, MX98.1, U1.20
col13: MACRO2.1, MACRO3.1, MACRO4.1, MX65.1, MX83.1, MX92.1, U1.19
col14: MX18.1, MX34.1, MX84.1, MX85.1, MX93.1, MX95.1, U1.18
col15: MX2.1, MX19.1, MX35.1, MX51.1, MX62.1, MX101.1, U1.31
col16: MX3.1, MX20.1, MX36.1, MX52.1, MX63.1, U1.28
col17: MX4.1, MX21.1, MX37.1, MX53.1, MX102.1, U1.29
col18: MX5.1, MX22.1, MX54.1, MX99.1, MX100.1, U1.30
row1: D2.1, D3.1, D4.1, D5.1, D69.1, D70.1, D71.1, D72.1, D73.1, D74.1, D75.1, D76.1, D77.1, D78.1, D79.1, D80.1, D81.1, D82.1, D83.1, U1.25
row2: D6.1, D7.1, D8.1, D9.1, D10.1, D11.1, D12.1, D13.1, D14.1, D15.1, D16.1, D17.1, D18.1, D19.1, D20.1, D21.1, D22.1, D49.1, D66.1, U1.26
row3: D1.1, D23.1, D24.1, D25.1, D26.1, D27.1, D28.1, D29.1, D30.1, D31.1, D32.1, D33.1, D34.1, D35.1, D36.1, D37.1, D67.1, D86.1, D87.1, U1.27
row4: D38.1, D39.1, D40.1, D41.1, D42.1, D43.1, D44.1, D45.1, D46.1, D47.1, D48.1, D50.1, D51.1, D52.1, D53.1, D54.1, D68.1, D84.1, D85.1, U1.32
row5: D55.1, D56.1, D57.1, D58.1, D59.1, D60.1, D61.1, D62.1, D63.1, D64.1, D65.1, D88.1, D89.1, D90.1, U1.1

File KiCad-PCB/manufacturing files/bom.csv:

Comment,Designator,Footprint,LCSC
"1uF","C11,C5,C6,C7,C8","Capacitor_SMD:C_0805_2012Metric",""
"104","C3,C2,C1,C4,C12,C13,C14,C15,C16,C17,C18,C19,C20,C23,C24,C22,C25,C26,C21,C32,C31,C30,C33,C34,C35,C36,C37,C38,C39,C40,C41,C42,C29,C28,C27,C48,C47,C46,C49,C50,C51,C52,C53,C54,C45,C44,C43,C55,C56,C57","Capacitor_SMD:C_0805_2012Metric",""
"22pF","C9,C10","Capacitor_SMD:C_0805_2012Metric",""
"SOD-123","D2,D3,D4,D5,D6,D7,D8,D9,D10,D11,D12,D13,D14,D15,D16,D17,D18,D19,D20,D21,D22,D23,D24,D25,D26,D27,D28,D29,D30,D31,D32,D33,D34,D35,D36,D37,D38,D39,D40,D41,D42,D43,D44,D45,D46,D47,D50,D51,D52,D53,D54,D55,D56,D57,D58,D59,D60,D61,D62,D63,D1,D48,D49,D64,D79,D80,D81,D82,D75,D76,D77,D78,D71,D72,D73,D74,D69,D70,D83,D84,D85,D86,D87,D88,D90,D65,D66,D67,D68,D89","Diode_SMD:D_SOD-123",""
"Conn_01x04_Female","J1","Connector_JST:JST_SH_SM04B-SRSS-TB_1x04-1MP_P1.00mm_Horizontal",""
"WS2812B","LED6,LED5,LED4,LED7,LED8,LED9,LED10,LED11,LED12,LED13,LED14,LED15,LED16,LED3,LED17,LED2,LED18,LED19,LED1,LED25,LED24,LED23,LED26,LED27,LED28,LED29,LED30,LED31,LED32,LED33,LED34,LED35,LED22,LED21,LED20,LED41,LED40,LED39,LED42,LED43,LED44,LED45,LED46,LED47,LED38,LED37,LED36,LED48,LED49,LED50","LED_SMD:LED_WS2812B_PLCC4_5.0x5.0mm_P3.2mm",""
"MX-NoLED","MX2,MX3,MX4,MX5,MX7,MX8,MX9,MX10,MX11,MX12,MX13,MX14,MX15,MX16,MX17,MX19,MX20,MX21,MX24,MX25,MX26,MX27,MX28,MX29,MX30,MX31,MX32,MX33,MX35,MX36,MX37,MX39,MX40,MX41,MX42,MX43,MX44,MX45,MX46,MX47,MX51,MX52,MX53,MX63,MX48,MX49,MX64,MX80,MX81,MX82,MX83,MX76,MX77,MX78,MX79,MX72,MX73,MX74,MX75,MX70,MX71,MX84,MX91,MX88,MX95,MX97,MX98,MX99,MX100,MX102,MX101,MACRO1,MACRO2,MACRO3,MACRO4,MACRO5","MX_Alps_Hybrid:MX-1U-NoLED",""
"MX-NoLED","MX22,MX54,MX85","MX_Alps_Hybrid:MX-2U-NoLED",""
"MX-NoLED","MX23,MX94","MX_Alps_Hybrid:MX-1.75U-NoLED",""
"MX-NoLED","MX34,MX38","MX_Alps_Hybrid:MX-2.25U-NoLED",""
"MX-NoLED","MX50","MX_Alps_Hybrid:MX-2.75U-NoLED",""
"MX-NoLED","MX55,MX56,MX57,MX59,MX60,MX61,MX1,MX65,MX96","MX_Alps_Hybrid:MX-1.25U-NoLED",""
"MX-NoLED","MX58","MX_Alps_Hybrid:MX-6.25U-ReversedStabilizers-NoLED",""
"MX-NoLED","MX6,MX18,MX90,MX92,MX87,MX89","MX_Alps_Hybrid:MX-1.5U-NoLED",""
"MX-NoLED","MX62","MX_Alps_Hybrid:MX-2U-ReversedStabilizers-NoLED",""
"MX-NoLED","MX86","MX_Alps_Hybrid:MX-7U-ReversedStabilizers-NoLED",""
"MX-NoLED","MX93","MX_Alps_Hybrid:MX-ISO",""
"500ohm","R1","Resistor_SMD:R_0805_2012Metric",""
"10K","R5,R4","Resistor_SMD:R_0805_2012Metric",""
"SW_Push","SW1","random-keyboard-parts:SKQG-1155865",""
"ATmega32U4-AU","U1","Package_QFP:TQFP-44_10x10mm_P0.8mm",""
"Crystal_GND24_Small","Y1","Crystal:Crystal_SMD_3225-4Pin_3.2x2.5mm",""

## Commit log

2021-04-01 screwholes shrunk
    screw holes on feet and daughterboard screws were too big; shrunk to accommodate threading
2021-08-17 Case lasercut update
